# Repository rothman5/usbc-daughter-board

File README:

# USB Type C External Daughter Board
# designed by Rasheed Othman

This board is meant to be used in combination with my Mech-Eighty keyboard.

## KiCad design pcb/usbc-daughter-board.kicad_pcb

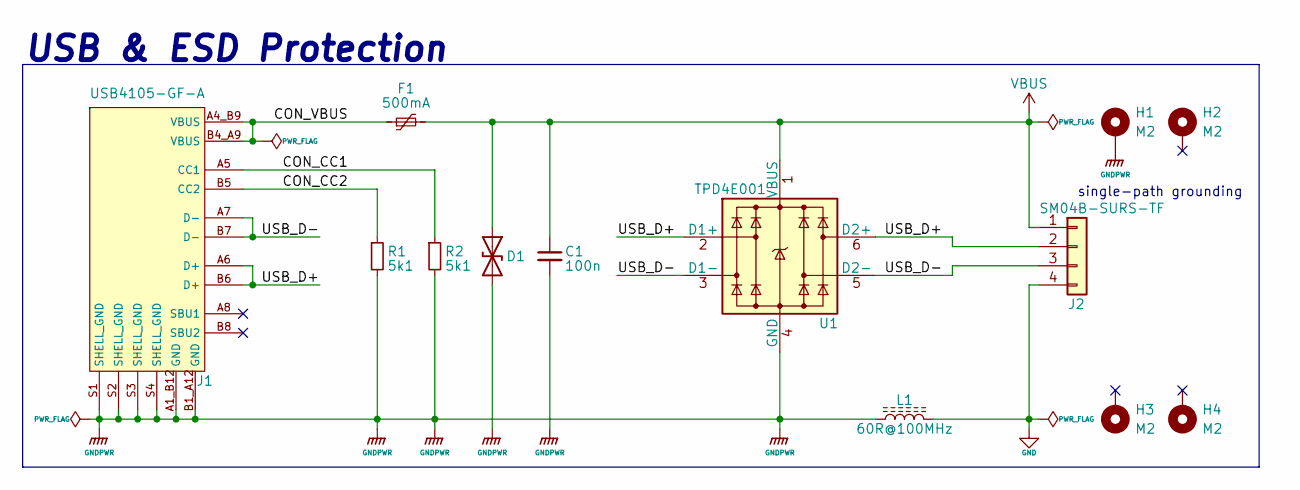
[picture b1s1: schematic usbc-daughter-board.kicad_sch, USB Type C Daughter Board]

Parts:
C1: 100n; C_0603_1608Metric; Manufacturer Part Number CC0603KRX7R9BB104; LCSC Part Number C14663
D1: D_TVS; D_SOD-123; Manufacturer Part # ATV02W5V0B-HF; Mouser Part # 750-ATV02W5V0B-HF
F1: 500mA; Fuse_0603_1608Metric; Manufacturer Part Number BSMD0603-050-6V; LCSC Part Number C883095
H1, H2, H3, H4: M2; MountingHole_2.2mm_M2_Pad
J1: USB4105-GF-A; USB_C_Receptacle_GCT_USB4105-GF-A
J2: SM04B-SURS-TF; JST_SUR_SM04B-SURS-TF_1x04-1MP_P0.80mm_Horizontal; Manufacturer Part # SM04B-SURS-TF(LF)(SN); Digikey Part # 455-3589-1-ND
L1: 60R@100MHz; L_0603_1608Metric; Manufacturer Part # MAF1608GAD471LTAH0; Mouser Part # 810-MAF1608GAD471LTA
R1, R2: 5k1; R_0603_1608Metric; Manufacturer Part Number 0603WAF5101T5E; LCSC Part Number C23186
U1: TPD4E001; SOT-23-6; Manufacturer Part # TPD4E001QDBVRQ1; Mouser Part # 595-TPD4E001QDBVRQ1

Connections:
/CON_CC1: J1.A5 (CC1), R2.1
/CON_CC2: J1.B5 (CC2), R1.1
/CON_VBUS: F1.1, J1.A4_B9 (VBUS), J1.B4_A9 (VBUS)
/USB_D+: J1.A6 (D+), J1.B6 (D+), J2.2, U1.2 (D1+), U1.6 (D2+)
/USB_D-: J1.A7 (D-), J1.B7 (D-), J2.3, U1.3 (D1-), U1.5 (D2-)
GND: J2.4, L1.2
GNDPWR: C1.2, D1.2 (A2), H1.1, J1.A1_B12 (GND), J1.B1_A12 (GND), J1.S1 (SHELL_GND), J1.S2 (SHELL_GND), J1.S3 (SHELL_GND), J1.S4 (SHELL_GND), L1.1, R1.2, R2.2, U1.4 (GND)
VBUS: C1.1, D1.1 (A1), F1.2, J2.1, U1.1 (VBUS)

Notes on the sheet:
single-path grounding
USB & ESD Protection

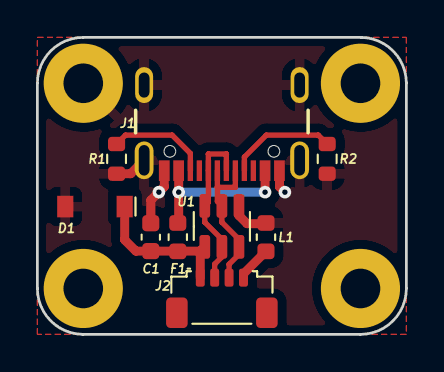
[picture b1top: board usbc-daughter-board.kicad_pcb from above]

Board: 2 copper layers, 20.5 x 16.5 mm, 13 parts (0 on the bottom side), 8 nets.

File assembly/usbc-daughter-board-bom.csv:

"Source:","D:\kicad-workspace\usbc-daughter-board\pcb\usbc-daughter-board.kicad_sch"
"Date:","2022-07-11 9:58:13 AM"
"Tool:","Eeschema (6.0.5)"
"Generator:","D:\program-files\kicad\bin\scripting\plugins/bom_csv_grouped_by_value_with_fp.py"
"Component Count:","13"
"Designator","Quantity","Value","Footprint","Manufacturer","Manufacturer Part #","Digikey Part #"
"C1, ","1","100n","Capacitor_SMD:C_0603_1608Metric","Samsung Electro-Mechanics","CL10B104KB8NNWC","1276-1935-1-ND"
"D1, ","1","D_TVS","Diode_SMD:D_SOD-123","Comchip Technology","ATV02W5V0B-HF","641-1986-1-ND"
"F1, ","1","500mA","Fuse:Fuse_0603_1608Metric","Littelfuse Inc.","1206L050/15YR","F3733CT-ND"
"H1, H2, H3, H4, ","4","M2","MountingHole:MountingHole_2.2mm_M2_Pad","","",""
"J1, ","1","USB4105-GF-A","Connector_USB:USB_C_Receptacle_GCT_USB4105-GF-A","","",""
"J2, ","1","SM04B-SURS-TF","Connector_JST:JST_SUR_SM04B-SURS-TF_1x04-1MP_P0.80mm_Horizontal","JST Sales America Inc.","SM04B-SURS-TF(LF)(SN)","455-3589-1-ND"
"L1, ","1","60R@100MHz","Inductor_SMD:L_0603_1608Metric","TDK Corporation","MAF1608GAD471LTAH0","445-181517-1-ND"
"R1, R2, ","2","5k1","Resistor_SMD:R_0603_1608Metric","Stackpole Electronics Inc.","RMCF0603FT5K10","RMCF0603FT5K10CT-ND"
"U1, ","1","TPD4E001","Package_TO_SOT_SMD:SOT-23-6","Texas Instruments ","TPD4E001QDBVRQ1","296-39344-1-ND"

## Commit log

2022-07-03 Final product
2022-07-03 Readme added
2022-07-03 Added preview images
2022-07-03 Added preview images to ReadMe
2022-07-11 Added gerbers
2022-07-11 Readme updated
